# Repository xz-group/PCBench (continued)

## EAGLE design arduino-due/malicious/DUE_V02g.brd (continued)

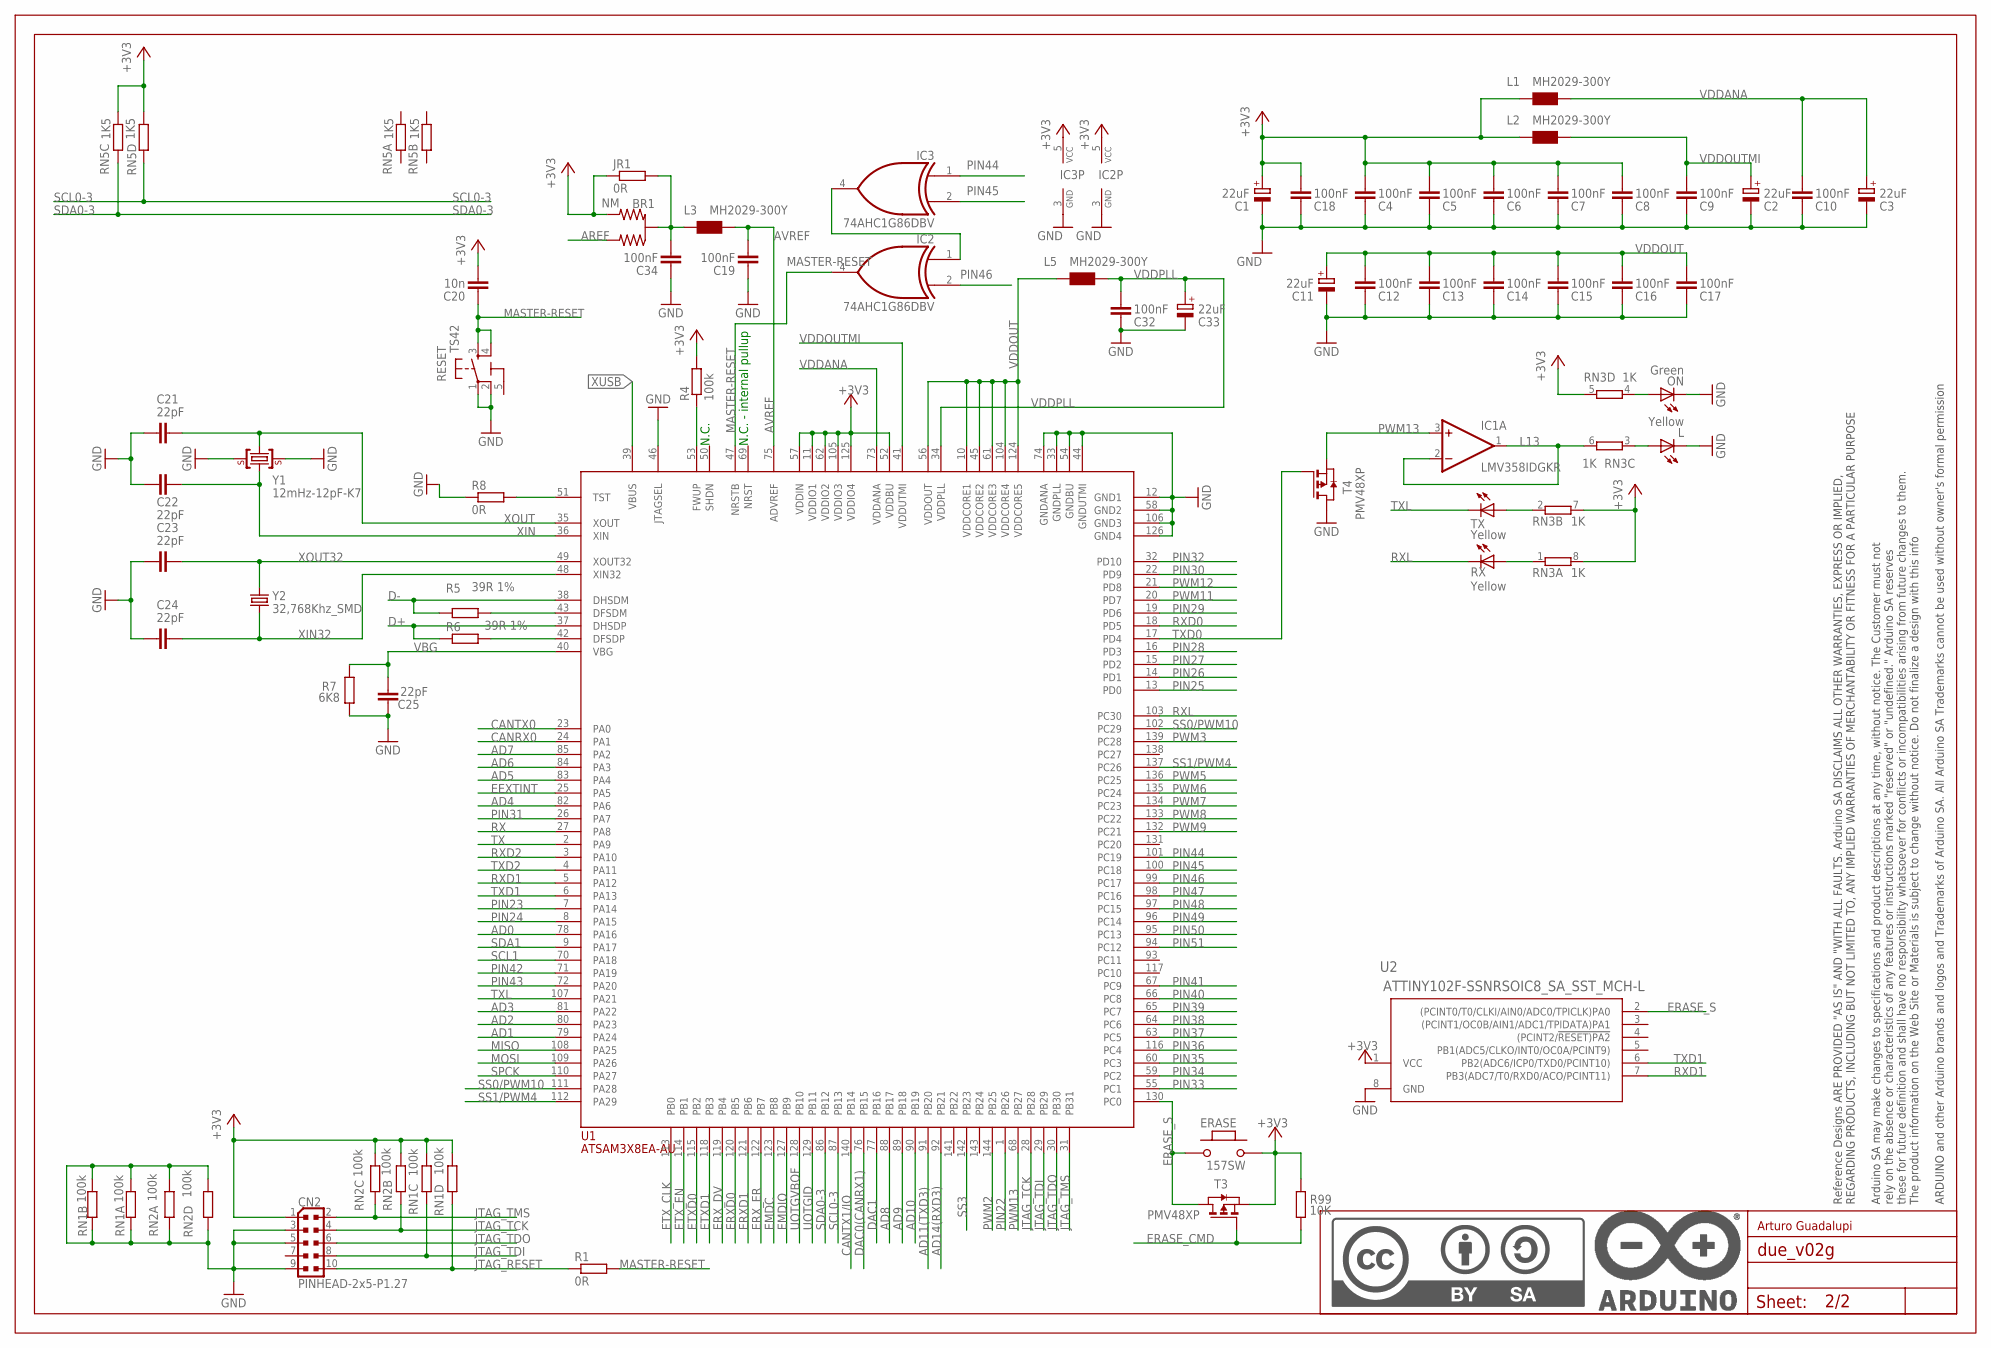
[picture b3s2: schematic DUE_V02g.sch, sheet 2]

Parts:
BR1: NM; J0402
C1, C2, C3, C11, C33: 22uF; SMC_B
C4, C5, C6, C7, C8, C9, C10, C12, C13, C14, C15, C16, C17, C18, C19, C32, C34: 100nF; C0402
C20: 10n; C0402
C21, C22, C23, C24, C25: 22pF; C0402
CN2: PINHEAD-2x5-P1.27; PINHEAD_2X05_127
ERASE: 157SW; SMD_157SW
IC1: LMV358IDGKR; MSOP08
IC2, IC3: 74AHC1G86DBV; SOT23-5
JR1: 0R; R0402
L: Yellow; CHIPLED_0805
L1, L2, L3, L5: MH2029-300Y; 0805
ON: Green; CHIPLED_0805
R1, R8: 0R; R0402
R4: 100k; R0402
R5, R6: 39R 1%; R0402
R7: 6K8; R0603-ROUND
R99: 10K; R0402
RESET: TS42
RN1, RN2: 100k; CAY16
RN3: 1K; CAY16
RN5: 1K5; CAY16
RX: Yellow; CHIPLED_0805
T3, T4: PMV48XP; SOT-23
TX: Yellow; CHIPLED_0805
U1: ATSAM3X8EA-AU; LQFP144
U2: ATTINY102F-SSNRSOIC8_SA_SST_MCH-L; SOIC8_SA_SST_MCH-L
U$2: DNP; FRAME
Y1: 12mHz-12pF-K7; CRYSTAL-3.2-2.5
Y2: 32,768Khz_SMD; RESONATOR_EPSON_FC_145

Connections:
5-GND: RESET.5 (5-GND)
+3V3: BR1.3 (2), C1.+, C4.2, C5.2, C6.2, C7.2, C8.2, C18.2, C20.2, CN2.1, ERASE.1, IC2.5 (VCC), IC3.5 (VCC), JR1.1, L1.1, L2.1, R4.2, R99.2, RN1.5 (2), RN1.6 (2), RN2.2 (1), RN2.3 (1), RN3.5 (2), RN3.7 (2), RN3.8 (2), RN5.3 (1), RN5.4 (1), T3.2 (S), U1.11 (VDDIO1), U1.52 (VDDBU), U1.57 (VDDIN), U1.62 (VDDIO2), U1.105 (VDDIO3), U1.125 (VDDIO4), U2.1 (VCC); also elsewhere on the board
AD0: U1.78 (PA16); also elsewhere on the board
AD1: U1.79 (PA24); also elsewhere on the board
AD2: U1.80 (PA23); also elsewhere on the board
AD3: U1.81 (PA22); also elsewhere on the board
AD4: U1.82 (PA6); also elsewhere on the board
AD5: U1.83 (PA4); also elsewhere on the board
AD6: U1.84 (PA3); also elsewhere on the board
AD7: U1.85 (PA2); also elsewhere on the board
AD8: U1.88 (PB17); also elsewhere on the board
AD9: U1.89 (PB18); also elsewhere on the board
AD10: U1.90 (PB19); also elsewhere on the board
AD11(TXD3): U1.91 (PB20); also elsewhere on the board
AD14(RXD3): U1.92 (PB21); also elsewhere on the board
AREF: BR1.1; also elsewhere on the board
AVREF: C19.2, L3.2, U1.75 (ADVREF)
AVREFL: BR1.2 (C), C34.2, JR1.2, L3.1
CANRX0: U1.24 (PA1); also elsewhere on the board
CANTX0: U1.23 (PA0); also elsewhere on the board
CANTX1/IO: U1.140 (PB14); also elsewhere on the board
D+: R6.1, U1.37 (DHSDP); also elsewhere on the board
D-: R5.1, U1.38 (DHSDM); also elsewhere on the board
DAC0(CANRX1): U1.76 (PB15); also elsewhere on the board
DAC1: U1.77 (PB16); also elsewhere on the board
EEXTINT: U1.25 (PA5)
EMDC: U1.123 (PB8)
EMDIO: U1.127 (PB9)
ERASE_CMD: R99.1, T3.3 (G); also elsewhere on the board
ERASE_S: ERASE.2, T3.1 (D), U1.130 (PC0), U2.2 ((PCINT0/T0/CLKI/AIN0/ADC0/TPICLK)PA0)
ERXD0: U1.120 (PB5)
ERXD1: U1.121 (PB6)
ERX_DV: U1.119 (PB4)
ERX_ER: U1.122 (PB7)
ETXD0: U1.115 (PB2)
ETXD1: U1.118 (PB3)
ETX_CLK: U1.113 (PB0)
ETX_EN: U1.114 (PB1)
GND: C1.-, C2.-, C3.-, C4.1, C5.1, C6.1, C7.1, C8.1, C9.1, C10.1, C11.-, C12.1, C13.1, C14.1, C15.1, C16.1, C17.1, C18.1, C19.1, C21.2, C22.2, C23.2, C24.2, C25.2, C32.1, C33.-, C34.1, CN2.3, CN2.5, CN2.9, IC2.3 (GND), IC3.3 (GND), L.C, ON.C, R7.1, R8.1, RESET.1, RESET.2, RN1.1, RN1.2 (1), RN1.7 (2), RN1.8 (2), RN2.1, RN2.4 (1), RN2.5 (2), RN2.8 (2), T4.1 (D), U1.12 (GND1), U1.33 (GNDPLL), U1.44 (GNDUTMI), U1.46 (JTAGSEL), U1.54 (GNDBU), U1.58 (GND2), U1.74 (GNDANA), U1.106 (GND3), U1.126 (GND4), U2.8 (GND), Y1.2 (GND), Y1.4 (GND); also elsewhere on the board
JTAG_RESET: CN2.10, R1.1, RN1.4 (1)
JTAG_TCK: CN2.4, RN2.7 (2), U1.28 (PB28); also elsewhere on the board
JTAG_TDI: CN2.8, RN1.3 (1), U1.29 (PB29)
JTAG_TDO: CN2.6, U1.30 (PB30)
JTAG_TMS: CN2.2, RN2.6 (2), U1.31 (PB31); also elsewhere on the board
L13: IC1.1 (OUT), IC1.2 (-IN), RN3.6 (2)
MASTER-RESET: C20.1, IC2.4 (O), R1.2, RESET.3, RESET.4, U1.47 (NRSTB); also elsewhere on the board
MISO: U1.108 (PA25); also elsewhere on the board
MOSI: U1.109 (PA26); also elsewhere on the board
unnamed: L.A, RN3.3 (1)
unnamed: ON.A, RN3.4 (1)
unnamed: R8.2, U1.51 (TST)
unnamed: R4.1, U1.53 (FWUP)
unnamed: R5.2, U1.43 (DFSDM)
unnamed: R6.2, U1.42 (DFSDP)
unnamed: IC2.1 (I0), IC3.4 (O)
unnamed: RN3.1, RX.A
unnamed: RN3.2 (1), TX.A
PIN22: U1.1 (PB26); also elsewhere on the board
PIN23: U1.7 (PA14); also elsewhere on the board
PIN24: U1.8 (PA15); also elsewhere on the board
PIN25: U1.13 (PD0); also elsewhere on the board
PIN26: U1.14 (PD1); also elsewhere on the board
PIN27: U1.15 (PD2); also elsewhere on the board
PIN28: U1.16 (PD3); also elsewhere on the board
PIN29: U1.19 (PD6); also elsewhere on the board
PIN30: U1.22 (PD9); also elsewhere on the board
PIN31: U1.26 (PA7); also elsewhere on the board
PIN32: U1.32 (PD10); also elsewhere on the board
PIN33: U1.55 (PC1); also elsewhere on the board
PIN34: U1.59 (PC2); also elsewhere on the board
PIN35: U1.60 (PC3); also elsewhere on the board
PIN36: U1.116 (PC4); also elsewhere on the board
PIN37: U1.63 (PC5); also elsewhere on the board
PIN38: U1.64 (PC6); also elsewhere on the board
PIN39: U1.65 (PC7); also elsewhere on the board
PIN40: U1.66 (PC8); also elsewhere on the board
PIN41: U1.67 (PC9); also elsewhere on the board
PIN42: U1.71 (PA19); also elsewhere on the board
PIN43: U1.72 (PA20); also elsewhere on the board
PIN44: IC3.1 (I0), U1.101 (PC19); also elsewhere on the board
PIN45: IC3.2 (I1), U1.100 (PC18); also elsewhere on the board
PIN46: IC2.2 (I1), U1.99 (PC17); also elsewhere on the board
PIN47: U1.98 (PC16); also elsewhere on the board
PIN48: U1.97 (PC15); also elsewhere on the board
PIN49: U1.96 (PC14); also elsewhere on the board
PIN50: U1.95 (PC13); also elsewhere on the board
PIN51: U1.94 (PC12); also elsewhere on the board
PWM2: U1.144 (PB25); also elsewhere on the board
PWM3: U1.139 (PC28); also elsewhere on the board
PWM5: U1.136 (PC25); also elsewhere on the board
PWM6: U1.135 (PC24); also elsewhere on the board
PWM7: U1.134 (PC23); also elsewhere on the board
PWM8: U1.133 (PC22); also elsewhere on the board
PWM9: U1.132 (PC21); also elsewhere on the board
PWM11: U1.20 (PD7); also elsewhere on the board
PWM12: U1.21 (PD8); also elsewhere on the board
PWM13: IC1.3 (+IN), T4.2 (S), U1.68 (PB27); also elsewhere on the board
RX: U1.27 (PA8); also elsewhere on the board
RXD0: U1.18 (PD5); also elsewhere on the board
RXD1: U1.5 (PA12), U2.7 (PB3(ADC7/T0/RXD0/ACO/PCINT11)); also elsewhere on the board
RXD2: U1.3 (PA10); also elsewhere on the board
RXL: RX.C, U1.103 (PC30)
SCL0-3: RN5.5 (2), U1.87 (PB13); also elsewhere on the board
SCL1: U1.70 (PA18); also elsewhere on the board
SDA0-3: RN5.6 (2), U1.86 (PB12); also elsewhere on the board
SDA1: U1.9 (PA17); also elsewhere on the board
SPCK: U1.110 (PA27); also elsewhere on the board
SS0/PWM10: U1.102 (PC29), U1.111 (PA28); also elsewhere on the board
SS1/PWM4: U1.112 (PA29), U1.137 (PC26); also elsewhere on the board
SS3: U1.142 (PB23)
TX: U1.2 (PA9); also elsewhere on the board
TXD0: T4.3 (G), U1.17 (PD4); also elsewhere on the board
TXD1: U1.6 (PA13), U2.6 (PB2(ADC6/ICP0/TXD0/PCINT10)); also elsewhere on the board
TXD2: U1.4 (PA11); also elsewhere on the board
TXL: TX.C, U1.107 (PA21)
UOTGID: U1.129 (PB11); also elsewhere on the board
UOTGVBOF: U1.128 (PB10); also elsewhere on the board
VBG: C25.1, R7.2, U1.40 (VBG)
VDDANA: C3.+, C10.2, L1.2, U1.73 (VDDANA)
VDDOUT: C11.+, C12.2, C13.2, C14.2, C15.2, C16.2, C17.2, L5.1, U1.10 (VDDCORE1), U1.45 (VDDCORE2), U1.56 (VDDOUT), U1.61 (VDDCORE3), U1.104 (VDDCORE4), U1.124 (VDDCORE5)
VDDOUTMI: C2.+, C9.2, L2.2, U1.41 (VDDUTMI)
VDDPLL: C32.2, C33.+, L5.2, U1.34 (VDDPLL)
XIN: C22.1, U1.36 (XIN), Y1.1 (C1)
XIN32: C24.1, U1.48 (XIN32), Y2.P$2 (2)
XOUT: C21.1, U1.35 (XOUT), Y1.3 (C2)
XOUT32: C23.1, U1.49 (XOUT32), Y2.P$1 (1)
XUSB: U1.39 (VBUS); also elsewhere on the board

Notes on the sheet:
N.C.
N.C. - internal pullup
Arturo Guadalupi

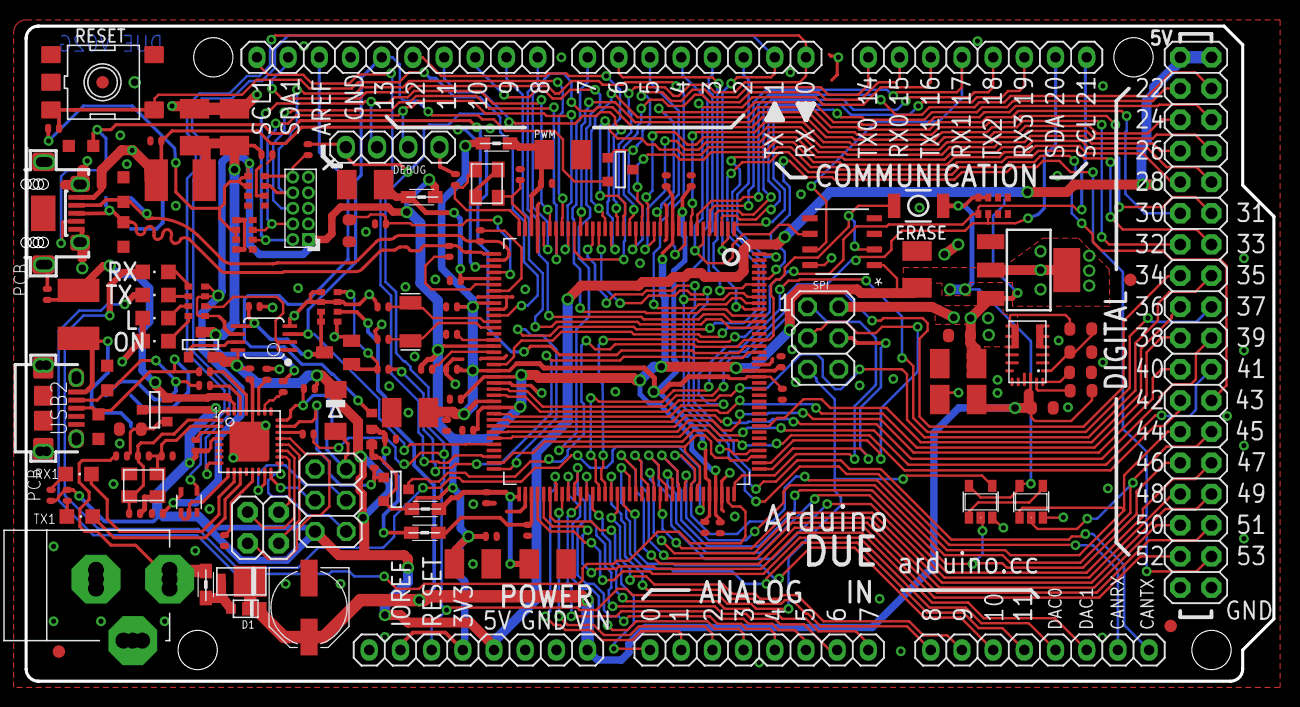
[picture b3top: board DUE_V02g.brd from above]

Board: 2 copper layers, 101.6 x 53.3 mm, 145 parts (0 on the bottom side), 151 nets.

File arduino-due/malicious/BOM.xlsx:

Qty | Value | Device | Package | Parts | Description | BUILT_BY | CASE | MANUFACTURER_PART_NUMBER | PART_NUMBER | TYPE | VALUE
1 |  | 0644_4X1VP.2,54H11,8 | PH1X4-THT | DEBUG | 4x1 V P.2,54 H11,8
3 | 0R | 0039_JUMP_0402 | R0402 | JR1, R1, R8 | 0R 0402 |  | 0402 |  | JUMP_0402 | Resistenze | 0R
1 | 100K_1% | 2022_CR0603FW104L | R0603-ROUND | R28 | 0603 Resistor 100K 1% |  |  |  | CR0603FW104L |  | 100K_1%
1 | 100k | 0026_100K_0603 | R0603-ROUND | R30 | 100K 0603 |  | 0603 |  | 100K_0603 | Resistenze | 100k
2 | 100k | 0134_CR0402FX1003L | R0402 | R4, R16 | 100K 0402 |  | 0402 |  | CR0402FX1003 L | Resistenze | 100k
3 | 100k | 0168_CAY16-104J4LF | CAY16 | RN1, RN2, RN4 | 100K 064 R |  | SMD 3,2x1,6 |  | CAY16-104J4LF | Resistenze | 100k
2 | 100nF | 0015_100NF_0603 | C0603-ROUND | C41, C50 | 100nF 0603 50V |  | 0603 |  | cl10b104kbnc | Condensatori | 100nF
22 | 100nF | 0132_100NF_0402 | C0402 | C4, C5, C6, C7, C8, C9, C10, C12, C13, C14, C15, C16, C17, C18, C19, C28, C30, 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 | 100nF 0402 |  | 0402 |  | 100nF_0402 | Condensatori | 100nF
4 | 10K | 0136_CR0402FX1002_L | R0402 | R2, R13, R18, R99 | 10K 0402 |  | 0402 |  | CR0402FX1002_L | Resistenze | 10K
2 | 10n | 0165_10NF_0402 | C0402 | C20, C26 | 10nF 0402
1 | 12mHz-12pF-K7 | 0396_12MHZ-12PF-K7 | CRYSTAL-3.2-2.5 | Y1 | 12Mhz - K7 12pF - SMD |  |  |  |  |  | 12mHz-12pF-K7
1 | 157SW | 0173_IT-1185AP1C-160G-G_T&R | SMD_157SW | ERASE | Pushbutton 4x3 SMD H2,5mm |  |  |  | IT-1185AP1C-160G-G_T&R | Switches | 157SW
1 | 16Mhz-KX-7 | 0395_16.000MHZ__12PF | CRYSTAL-3.2-2.5 | Y4 | 16Mhz - K7 12pF - SMD |  |  |  | 16.000Mhz__12pF | Cristalli | 16Mhz-KX-7
1 | 18x2F-H8.5 | 1756_12TW323 | 2X18 | XIO | Female Gray Connector strip for Arduino 3V3 bases 18x2 F V h 8,5 p2,54 |  |  |  | 12TW323 | Connettori | 18x2F-H8.5
1 | 19K1_0,1% | 2339_ | R0603-ROUND | R29 | 19K1 0,1% 0603 |  | 0603 |  |  | Resistenze | 19K1_0,1%
1 | 1K | 0005_064R_1K_/_CAY16-102J4LF | CAY16 | RN3 | 1K 064R |  | SMD_3,2x1,6 |  | 064R_1K_/_CAY16-102J4LF | Resistenze | 1K
5 | 1K | 0140_1K_0402 | R0402 | R3, R14, R15, R21, R23 | 1K 0402 |  | 0402 |  | 1K_0402 | Resistenze | 1K
1 | 1K5 | 0163_1K5_ARRAY | CAY16 | RN5 | 1K5 064 R
1 | 1M | 0139_1M_0402 | R0402 | R9 | 1M 0402 |  | 0402 |  | 1M_0402 | Resistenze | 1M
1 | 1uF | 0133_1UF_0402 | C0402 | C38 | 1uF 0402 |  | 0402 |  | 1uF_0402 | Condensatori | 1uF
2 | 22R | 0468_22R_0402 | R0402 | R19, R20 | 22R 0402 |  | 0402 |  | 22R_0402 | Resistenze | 22R
7 | 22pF | 0137_22PF_0402 | C0402 | C21, C22, C23, C24, C25, C39, C40 | 22pF 0402 |  | 0402 |  | 22pF_0402 | Condensatori | 22pF
10 | 22uF | 0167_ | SMC_B | C1, C2, C3, C11, C27, C29, C33, C35, C49, PC2 | 22uF 25V |  |  |  |  | Condensatori | 22uF
1 | 2x2M - NM | XXXX_PINHD-2X2 | 2X02 | JP5 | PIN HEADER
1 | 32,768Khz_SMD | 0213_ABS07-32.768KHZ-T | RESONATOR_EPSON_FC_145 | Y2 | 32,768KHz - SMD |  |  |  | ABS07-32.768KHZ-T | Cristalli | 32,768Khz_SMD
2 | 39R 1% | 0138_39R_0402 | R0402 | R5, R6 | 39R 0402
1 | 47uF | 0113_47UF | PANASONIC_D | PC1 | 47uF |  |  |  | 47uF | Condensatori | 47uF
1 | 56k | 0411_56K_0603 | R0603-ROUND | R31 | 56K 0603 |  | 0603 |  | 56K_0603 | Resistenze | 56k
1 | 6K8 | 0164_6K8_0603 | R0603-ROUND | R7 | 6K8 0603 |  | 0603 |  | 6K8_0603 | Resistenze | 6K8
2 | 74AHC1G86DBV | 74AHC1G86DBV | SOT23-5 | IC2, IC3 | 2-input EXCLUSIV-OR gate
1 | 74LVC1G125DCKR | 0040_SN74LVC1G125DCKR | SC70-5 | IC10 | Single bus buffer with 3-state output |  | SC70 |  | SN74LVC1G125DCKR | Circuito_Integrato | 74LVC1G125DCKR
1 | 75K | 0376_CR0603FX7502_L | R0603-ROUND | R17 | 75K 0603 |  | 0603 |  | CR0603FX7502_L | Resistenze | 75K
1 | ATMEGA16U2-MU | 0007_ATMEGA16U2-MUR | MLF32 | IC6 | 8-bit Microcontroller with 16K Bytes of ISP Flash and USB Controller ATMEGA16U2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 |  | QFN32_5x5 |  | ATMEGA16U2-MUR | Circuito_Integrato | ATMEGA16U2-MU
1 | ATSAM3X8EA-AU | 0162_ATSAM3X8EA-AUAU | LQFP144 | U1 | AT91SAM ARM-based Flash MCU ATSAM3X8EA-AU |  | LQFP144 |  | ATSAM3X8EA-AU | Circuito_Integrato | ATSAM3X8EA-AU
1 | ATTINY102F-SSNRSOIC8_SA_SST_MCH-L | ATTINY102F-SSNRSOIC8_SA_SST_MCH-L | SOIC8_SA_SST_MCH-L | U2 |  | EMA_Molly |  | ATTINY102F-SSNR
1 | BC847B | 0169_BC847B | SOT23 | Q2 | BC847BSMD |  |  |  | BC847B | Transistor | BC847B
5 | BRNCG0603MLC-05E | 0010_BRNCG0603MLC-05E | CT/CN0603 | Z1, Z2, Z3, Z4, Z5 | CG0603MLC-05E |  |  |  | BRNCG0603MLC-05E | Protezione | BRNCG0603MLC-05E
1 | CD1206-S01575 | 0012_CD1206-S01575 | MINIMELF | D2 | small-signal high-speed Switching Diodes CD1206 |  | 1206 |  | CD1206-S01575 | Diodi | CD1206-S01575
5 | FH254-108DF08500V | 1683_20TW-536 | 1X08 | ADCH, ADCL, COMMUNICATION, POWER, PWML | Female Gray Connector strip for Arduino 3V3 bases - 8x1 F V h 8,5 p2,54mm |  |  |  | 20TW-536 | Connettori | FH254-108DF08500V
1 | FH254-110DF08500V | 1684_20TW-537 | 1X10 | PWMH | Female Gray Connector strip for Arduino 3V3 bases - 10x1 F V h 8,5 p2,54mm |  |  |  | 20TW-537 | Connettori | FH254-110DF08500V
4 | FIDUCIALMOUNT | FIDUCIALMOUNT | FIDUCIA-MOUNT | FID1, FID2, FID3, FID4
1 | Green | 0043_KPT-2012SGC | CHIPLED_0805 | ON | LED GREEN - SMD-0805 |  |  |  | KPT-2012SGC | Opto | Green
2 | ICSP | 0114_PH254-203DF118A00V | 2X03 | ICSP1, SPI | 3x2 M V h 8,5 mm p2,54 |  |  |  | PH254-203DF118A00V | Connettori | ICSP
1 | LMV358IDGKR | 0021_LMV358IDGKR | MSOP08 | IC1 | Dual low-voltage (2.7 V to 5.5 V), operational amplifiers with rail-to-rail out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 |  | MSOP8 |  | LMV358IDGKR | Circuito_Integrato | LMV358IDGKR
1 | MCR-AB1-S-RA-SMT-TR | 0631_MCR-AB1-S-RA-SMT-TR | MCR-AB1-S-RA-SMT | USB1 | Usb Micro F/90 Smd Tipo AB |  |  |  | MCR-AB1-S-RA-SMT-TR | Connettori | MCR-AB1-S-RA-SMT-TR
1 | MCR-B-S-RA-SMT-CS1TR | 0158_MCR-B-S-RA-SMT-CS1TR | CON2_USB_MICRO_B_AT | USB2 | Usb Micro F/90 Smd Tipo B |  |  |  | MCR-B-S-RA-SMT-CS1TR | Connettori | MCR-B-S-RA-SMT-CS1TR
2 | MF-MSMF050-2 500mA | 0002_MF-MSMF050-2 | L1812 | F1, F2 | 500 mA Multifuse � Polyfuse |  |  |  | MF-MSMF050-2 | Protezione | MF-MSMF050-2 500mA
5 | MH2029-300Y | 0001_BLM21PG300SN1D_/_MH2029-300Y | 805 | L1, L2, L3, L5, L6 | BLM21 |  |  |  | BLM21PG300SN1D_/_MH2029-300Y | Protezione | MH2029-300Y
1 | MPM3610 | 2093_MPM3610GQV-P | QFN-20 | IC5 | MPM3610 Step Down Regulator |  | QFN-20 |  | MPM3610GQV-P | Circuito_Integrato | MPM3610
1 | MSS1P3L-M3/89A | 1653_MSS1P3L-M3/89A | MICROSMP | D1 | Surface Mount Schottky Barrier Rectifiers - Case microSMP |  |  |  |  |  | MSS1P3L-M3/89A
1 | NM | J0402 | J0402 | BR1 | Three terminal jumper made from two 0402, 0603, 0805, etc.
1 | NX1117CE33Z | 0045_NX1117CE33Z,115 | SOT223 | IC4 | Low-dropout linear regulator 3V3 NX1117CE33Z,115 |  | SOT223 |  | NX1117CE33Z,115 | Circuito_Integrato | NX1117CE33Z
1 | PINHEAD-2x5-P1.27 | 0171_PH127-205DF055G00AROUND-PADS | PINHEAD_2X05_127 | CN2 | 2x5 PASSO 1,27
4 | PMV48XP | 0297_PMV48XP | SOT-23 | T1, T2, T3, T4 | 20 V, 3.5 A P-channel Trench MOSFET - PMV48XP |  | SOT23 |  | PMV48XP | Transistor | PMV48XP
1 | POWER-SUPPLY | 0018_19746-POWER-SUPPLY | POWERSUPPLY_DC-21MM | X2 | JACK |  |  |  | 19746 | Connettori | POWER-SUPPLY
1 | SS1P3L | 0025_SS1P3L-M3/84A | DO220AAL | D5 | 1A 30V Schottky Barrier Rectifiers -SS1P3L-M3/84A |  | SMP |  | SS1P3L-M3/84A | Diodi | SS1P3L
1 | TS42 | 0946_TS42031-160W-TR-7260 | TS42 | RESET | Pushbutton 6x6 Smd - White |  |  |  | IT-1157AHNP-160G-G_GTR | Switches | TS42
5 | Yellow | 0044_KPT-2012YC | CHIPLED_0805 | L, RX, RX1, TX, TX1 | LED YELLOW - SMD - 0805 |  |  |  | KPT-2012YC | Opto | Yellow

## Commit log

2020-10-16 arduino image
2020-10-16 Upload arduino due CAM
2020-11-19 Upload the benchmark of a13-olinuxino board.
2021-09-22 Update the schematic, layout, and test results of Arduino due
2021-09-22 Update the schematic and layout of 13
2021-09-22 trezor_one benchmark
2021-09-22 fix the links
